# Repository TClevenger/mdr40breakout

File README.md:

# mdr40breakout

Gerbers for a breakout board for 3M MDR-40 devices and cables, commonly used by IBM in its AS/400 line.  Requires a 3M 10240-55G3PC receptacle.

Current release is V1R2 (2026-04-30)

* Corrected pin numbering on silkscreen

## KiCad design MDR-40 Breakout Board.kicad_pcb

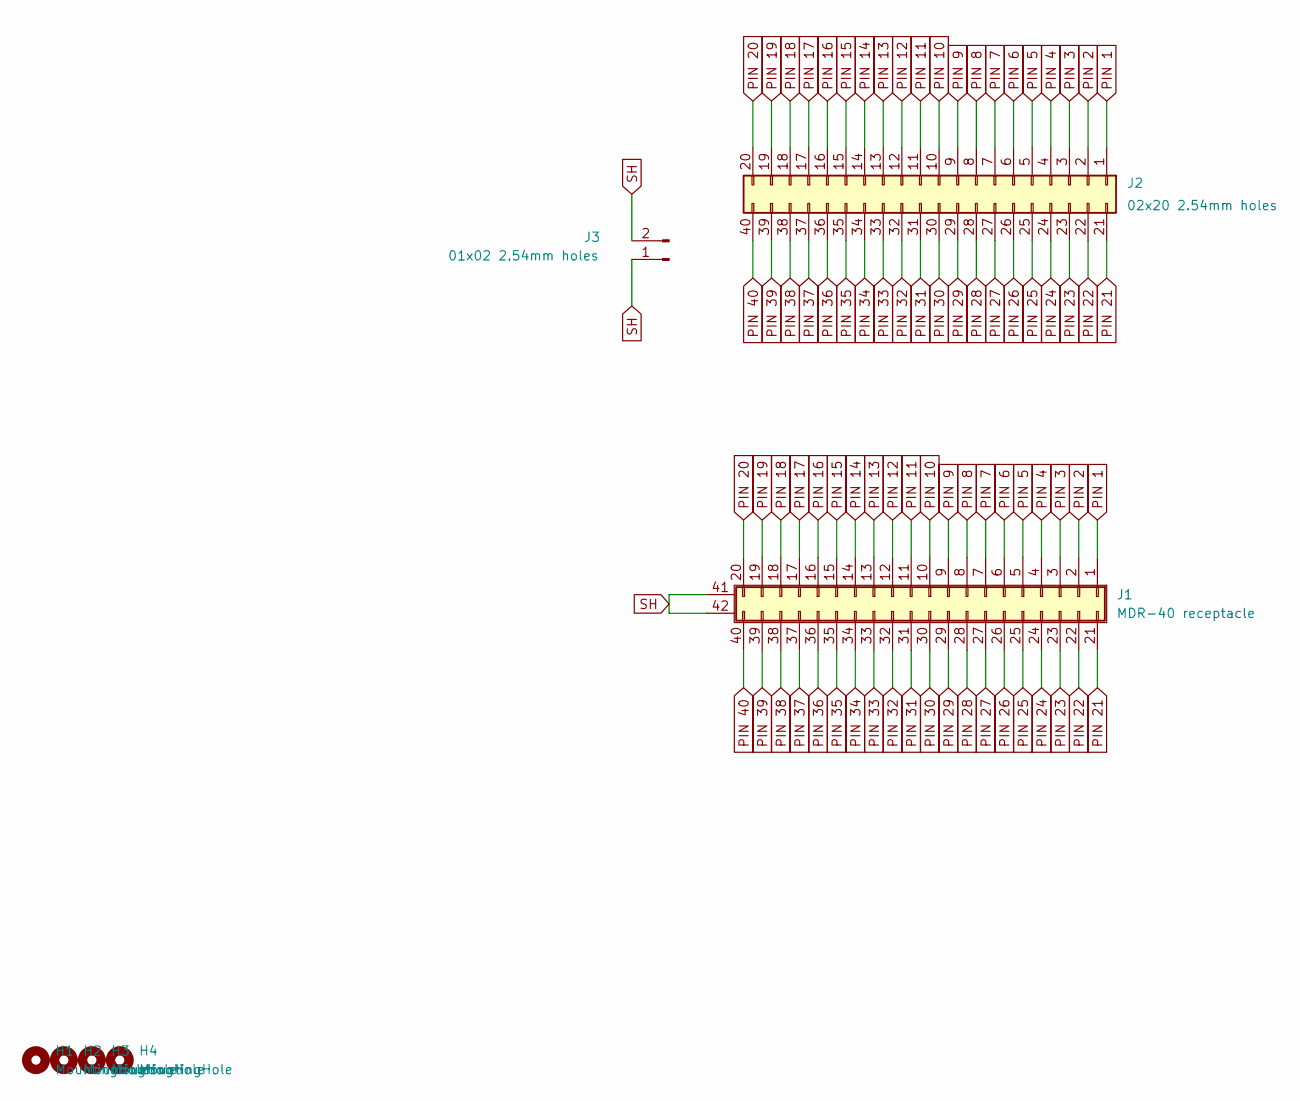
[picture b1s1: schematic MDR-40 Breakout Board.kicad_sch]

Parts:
H1, H2, H3, H4: MountingHole; MountingHole_3mm
J1: MDR-40 receptacle; 3M_10240-55G3PC
J2: 02x20 2.54mm holes; PinHeader_2x20_P2.54mm_Vertical
J3: 01x02 2.54mm holes; PinHeader_1x02_P2.54mm_Vertical

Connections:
PIN 1: J1.1, J2.1
PIN 2: J1.2, J2.2
PIN 3: J1.3, J2.3
PIN 4: J1.4, J2.4
PIN 5: J1.5, J2.5
PIN 6: J1.6, J2.6
PIN 7: J1.7, J2.7
PIN 8: J1.8, J2.8
PIN 9: J1.9, J2.9
PIN 10: J1.10, J2.10
PIN 11: J1.11, J2.11
PIN 12: J1.12, J2.12
PIN 13: J1.13, J2.13
PIN 14: J1.14, J2.14
PIN 15: J1.15, J2.15
PIN 16: J1.16, J2.16
PIN 17: J1.17, J2.17
PIN 18: J1.18, J2.18
PIN 19: J1.19, J2.19
PIN 20: J1.20, J2.20
PIN 21: J1.21, J2.21
PIN 22: J1.22, J2.22
PIN 23: J1.23, J2.23
PIN 24: J1.24, J2.24
PIN 25: J1.25, J2.25
PIN 26: J1.26, J2.26
PIN 27: J1.27, J2.27
PIN 28: J1.28, J2.28
PIN 29: J1.29, J2.29
PIN 30: J1.30, J2.30
PIN 31: J1.31, J2.31
PIN 32: J1.32, J2.32
PIN 33: J1.33, J2.33
PIN 34: J1.34, J2.34
PIN 35: J1.35, J2.35
PIN 36: J1.36, J2.36
PIN 37: J1.37, J2.37
PIN 38: J1.38, J2.38
PIN 39: J1.39, J2.39
PIN 40: J1.40, J2.40
SH: J1.41 (Shield), J1.42 (Shield), J3.1, J3.2

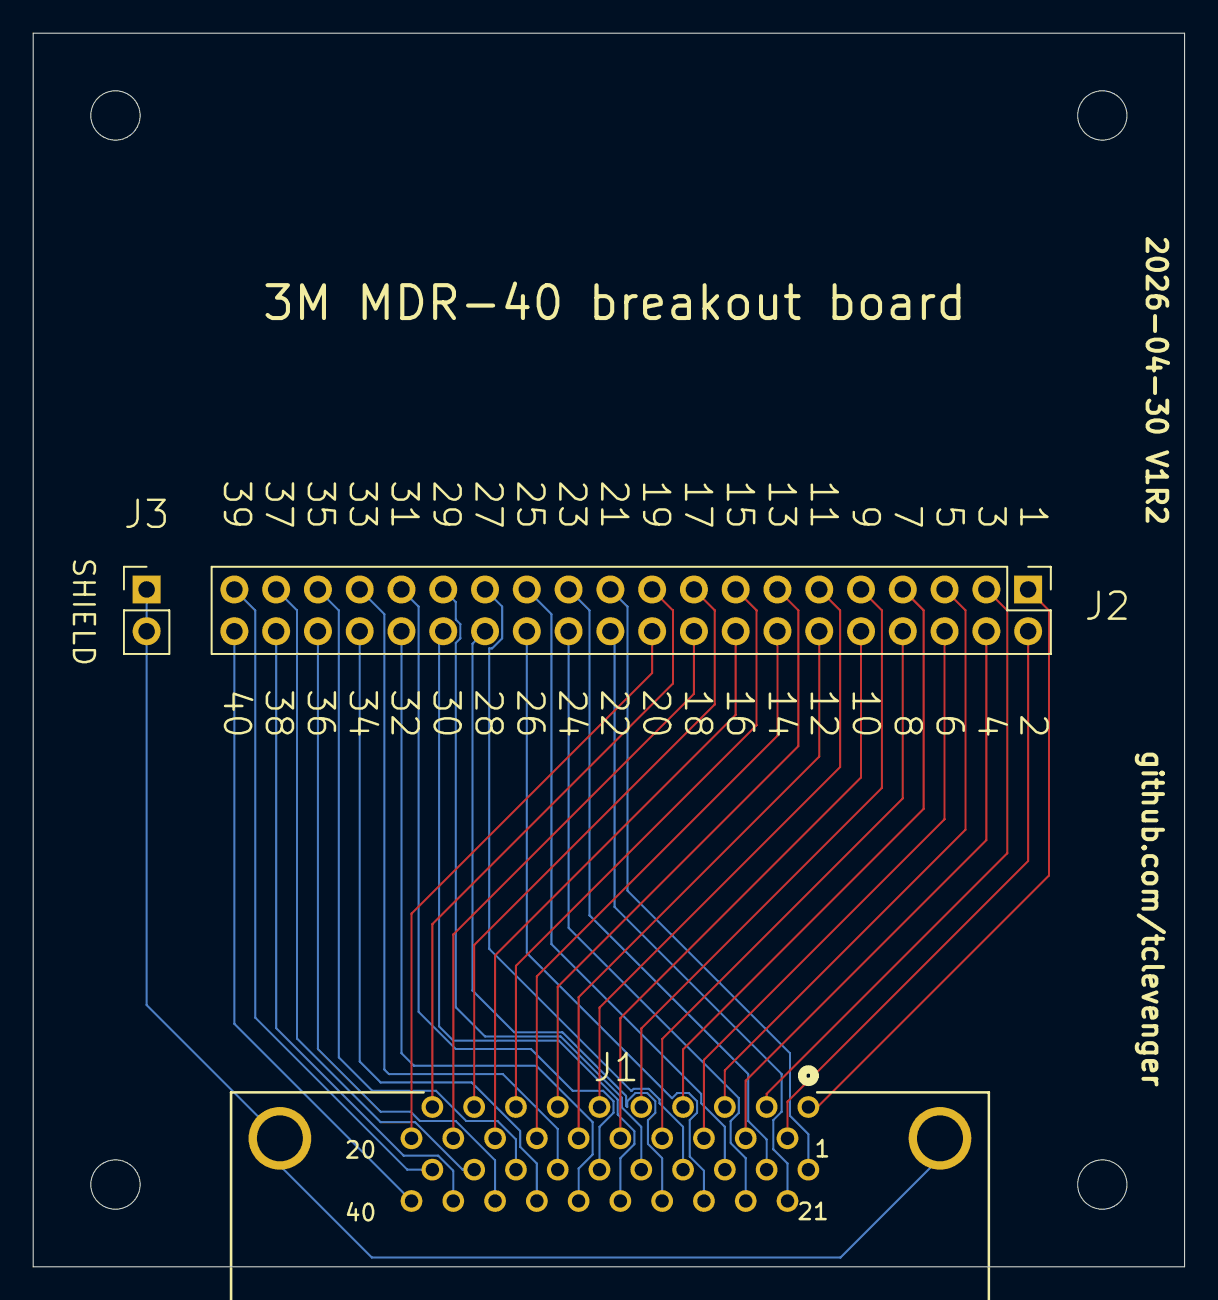
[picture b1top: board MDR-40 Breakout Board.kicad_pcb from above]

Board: 2 copper layers, 70.0 x 75.0 mm, 7 parts (0 on the bottom side), 41 nets.

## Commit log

2026-03-15 First upload
2026-04-06 Delete MDR-40 breakout board V1R1-.zip
    Replaced with V1R2
2026-04-06 Add files via upload
    IDC pins labeled incorrectly
2026-04-06 Add files via upload
    Updated image from V1R2
2026-04-30 V1R2 updates
